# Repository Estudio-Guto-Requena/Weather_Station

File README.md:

# Weather_Station
A prototiping code and hardware design to build a simple weatherstation

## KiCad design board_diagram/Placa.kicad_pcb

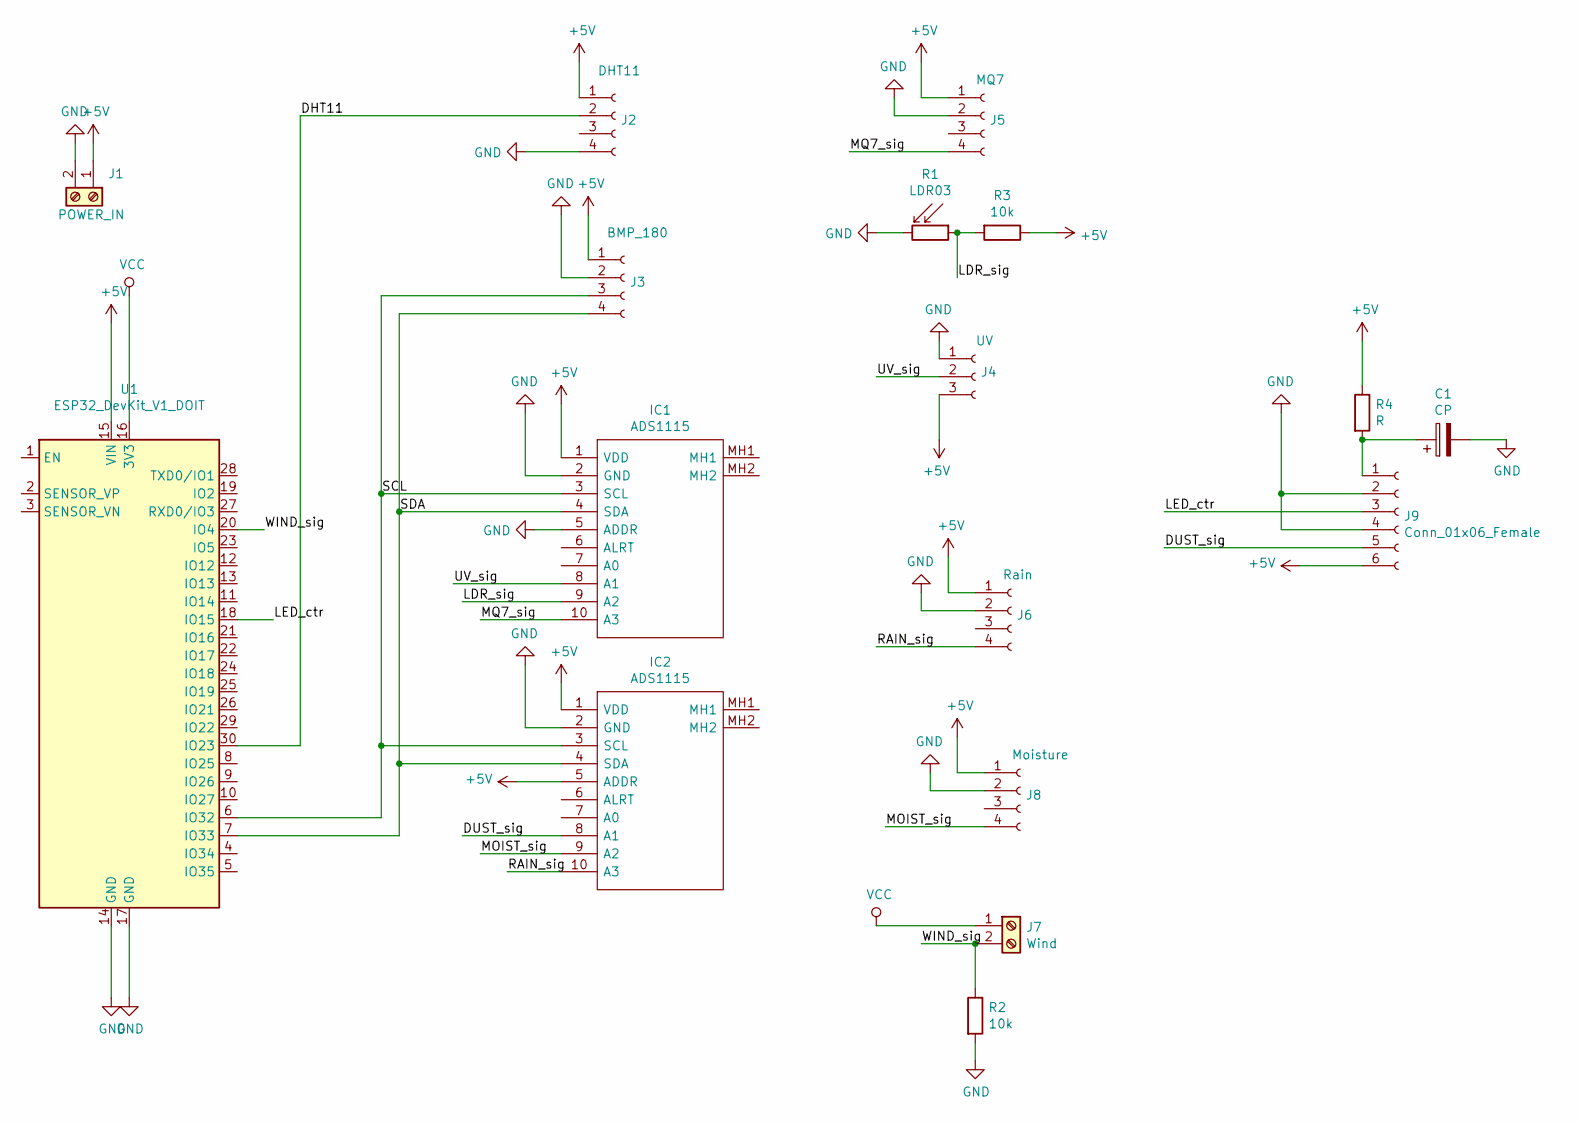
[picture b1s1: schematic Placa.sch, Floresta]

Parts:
C1: CP; CP_Radial_D6.3mm_P2.50mm
IC1, IC2: ADS1115; Manufacturer_Part_Number ADS1115
J1: POWER_IN; PhoenixContact_MCV_1,5_2-G-5.08_1x02_P5.08mm_Vertical
J2: DHT11; PinHeader_1x04_P2.54mm_Vertical
J3: BMP_180; PinHeader_1x04_P2.54mm_Vertical
J4: UV; PinHeader_1x03_P2.54mm_Vertical
J5: MQ7; PinHeader_1x04_P2.54mm_Vertical
J6: Rain; PinHeader_1x04_P2.54mm_Vertical
J7: Wind; PhoenixContact_MCV_1,5_2-G-5.08_1x02_P5.08mm_Vertical
J8: Moisture; PinHeader_1x04_P2.54mm_Vertical
J9: Conn_01x06_Female; PinHeader_1x06_P2.54mm_Vertical
R1: LDR03; R_LDR_10x8.5mm_P7.6mm_Vertical
R2, R3: 10k; R_Axial_DIN0207_L6.3mm_D2.5mm_P10.16mm_Horizontal
R4: R; R_Axial_DIN0207_L6.3mm_D2.5mm_P10.16mm_Horizontal
U1: ESP32_DevKit_V1_DOIT; esp32_devkit_v1_doit

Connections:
+5V: IC1.1 (VDD), IC2.1 (VDD), IC2.5 (ADDR), J1.1, J2.1, J3.1, J4.3, J5.1, J6.1, J8.1, J9.6, R3.1, R4.1, U1.15 (VIN)
/DHT11: J2.2, U1.30 (IO23)
/DUST_sig: IC2.8 (A1), J9.5
/LDR_sig: IC1.9 (A2), R1.1, R3.2
/LED_ctr: J9.3, U1.18 (IO15)
/MOIST_sig: IC2.9 (A2), J8.4
/MQ7_sig: IC1.10 (A3), J5.4
/RAIN_sig: IC2.10 (A3), J6.4
/SCL: IC1.3 (SCL), IC2.3 (SCL), J3.3, U1.6 (IO32)
/SDA: IC1.4 (SDA), IC2.4 (SDA), J3.4, U1.7 (IO33)
/UV_sig: IC1.8 (A1), J4.2
/WIND_sig: J7.2, R2.1, U1.20 (IO4)
GND: C1.2, IC1.2 (GND), IC1.5 (ADDR), IC2.2 (GND), J1.2, J2.4, J3.2, J4.1, J5.2, J6.2, J8.2, J9.2, J9.4, R1.2, R2.2, U1.14 (GND), U1.17 (GND)
unnamed: C1.1, J9.1, R4.2
VCC: J7.1, U1.16 (3V3)

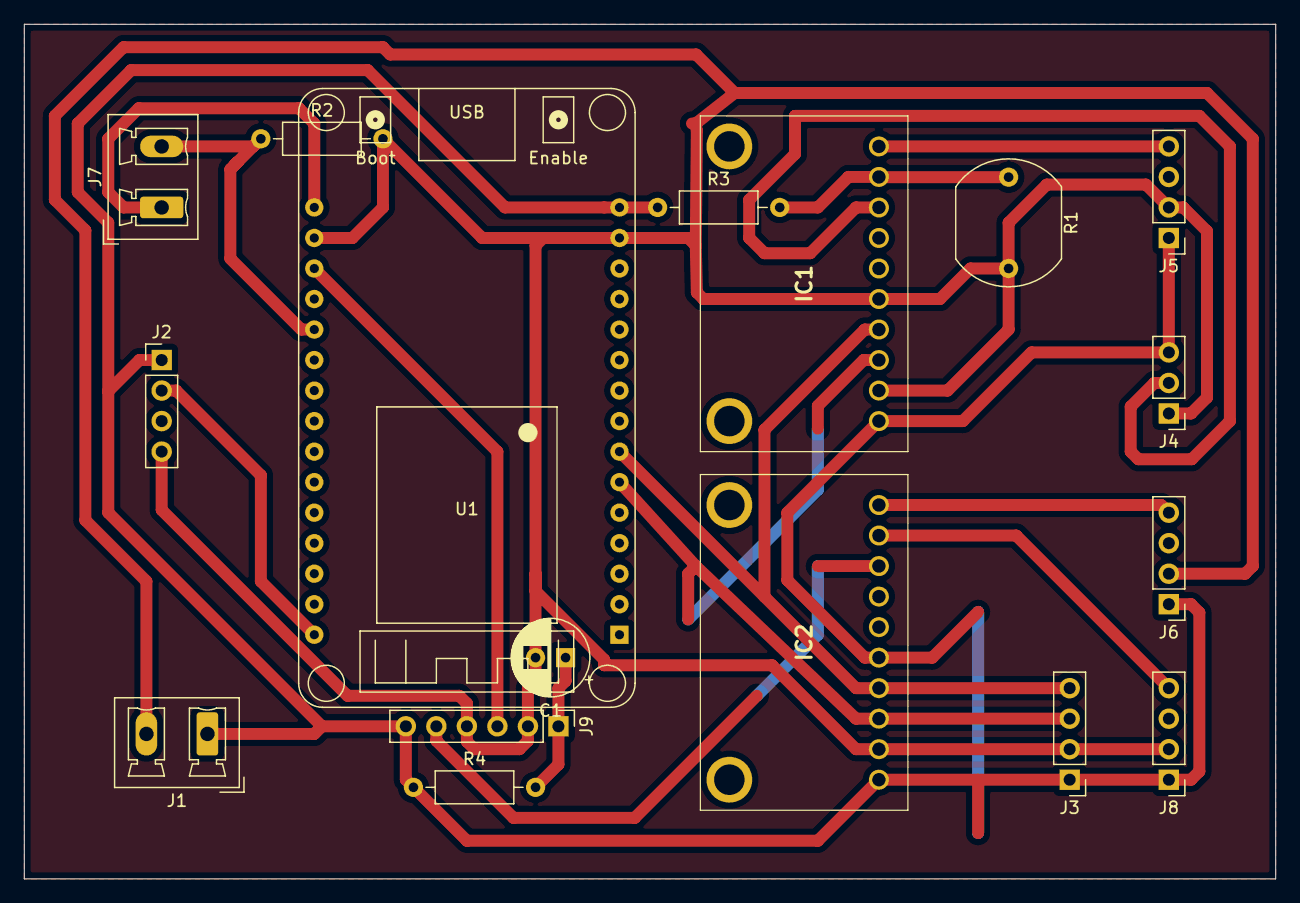
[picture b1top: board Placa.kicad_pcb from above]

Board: 2 copper layers, 104.1 x 71.1 mm, 17 parts (0 on the bottom side), 15 nets.

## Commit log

2022-08-08 Upload all project
